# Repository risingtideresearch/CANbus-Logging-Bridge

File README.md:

# CANbus-Logging-Bridge
Platform for collecting, logging, interpreting, and relaying CAN messages on multiple busses

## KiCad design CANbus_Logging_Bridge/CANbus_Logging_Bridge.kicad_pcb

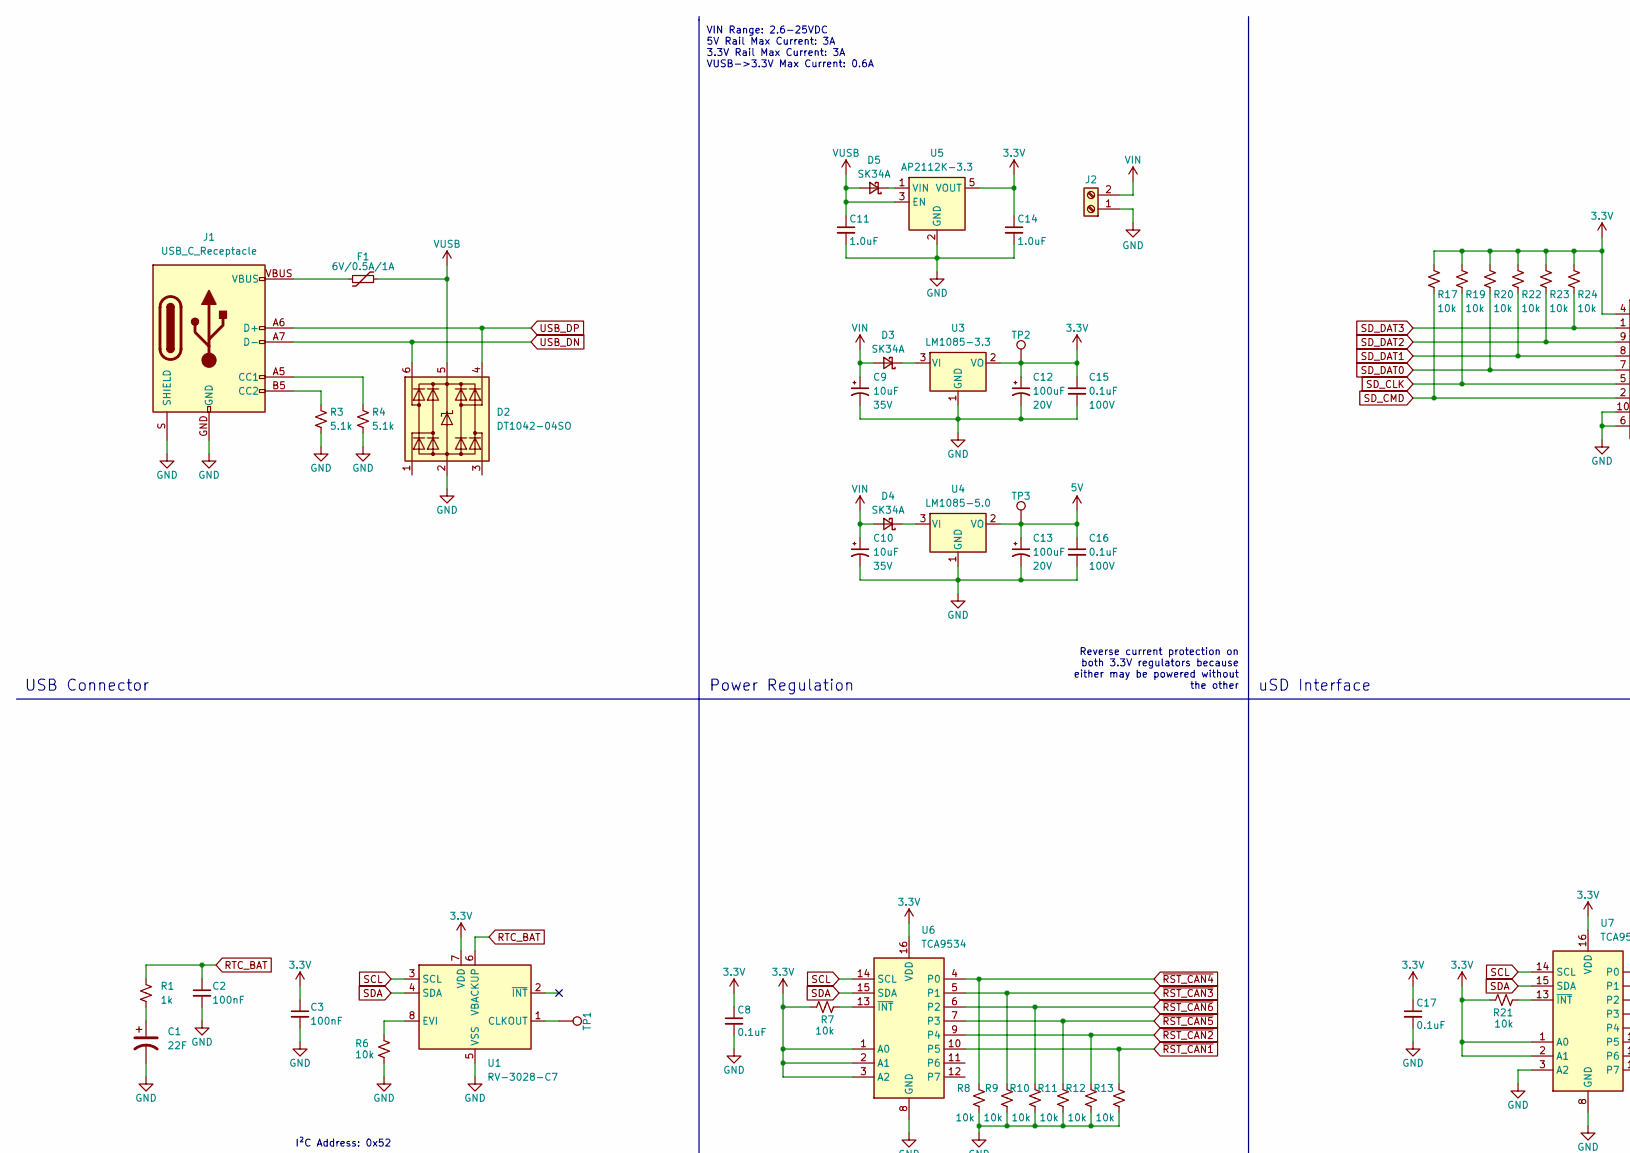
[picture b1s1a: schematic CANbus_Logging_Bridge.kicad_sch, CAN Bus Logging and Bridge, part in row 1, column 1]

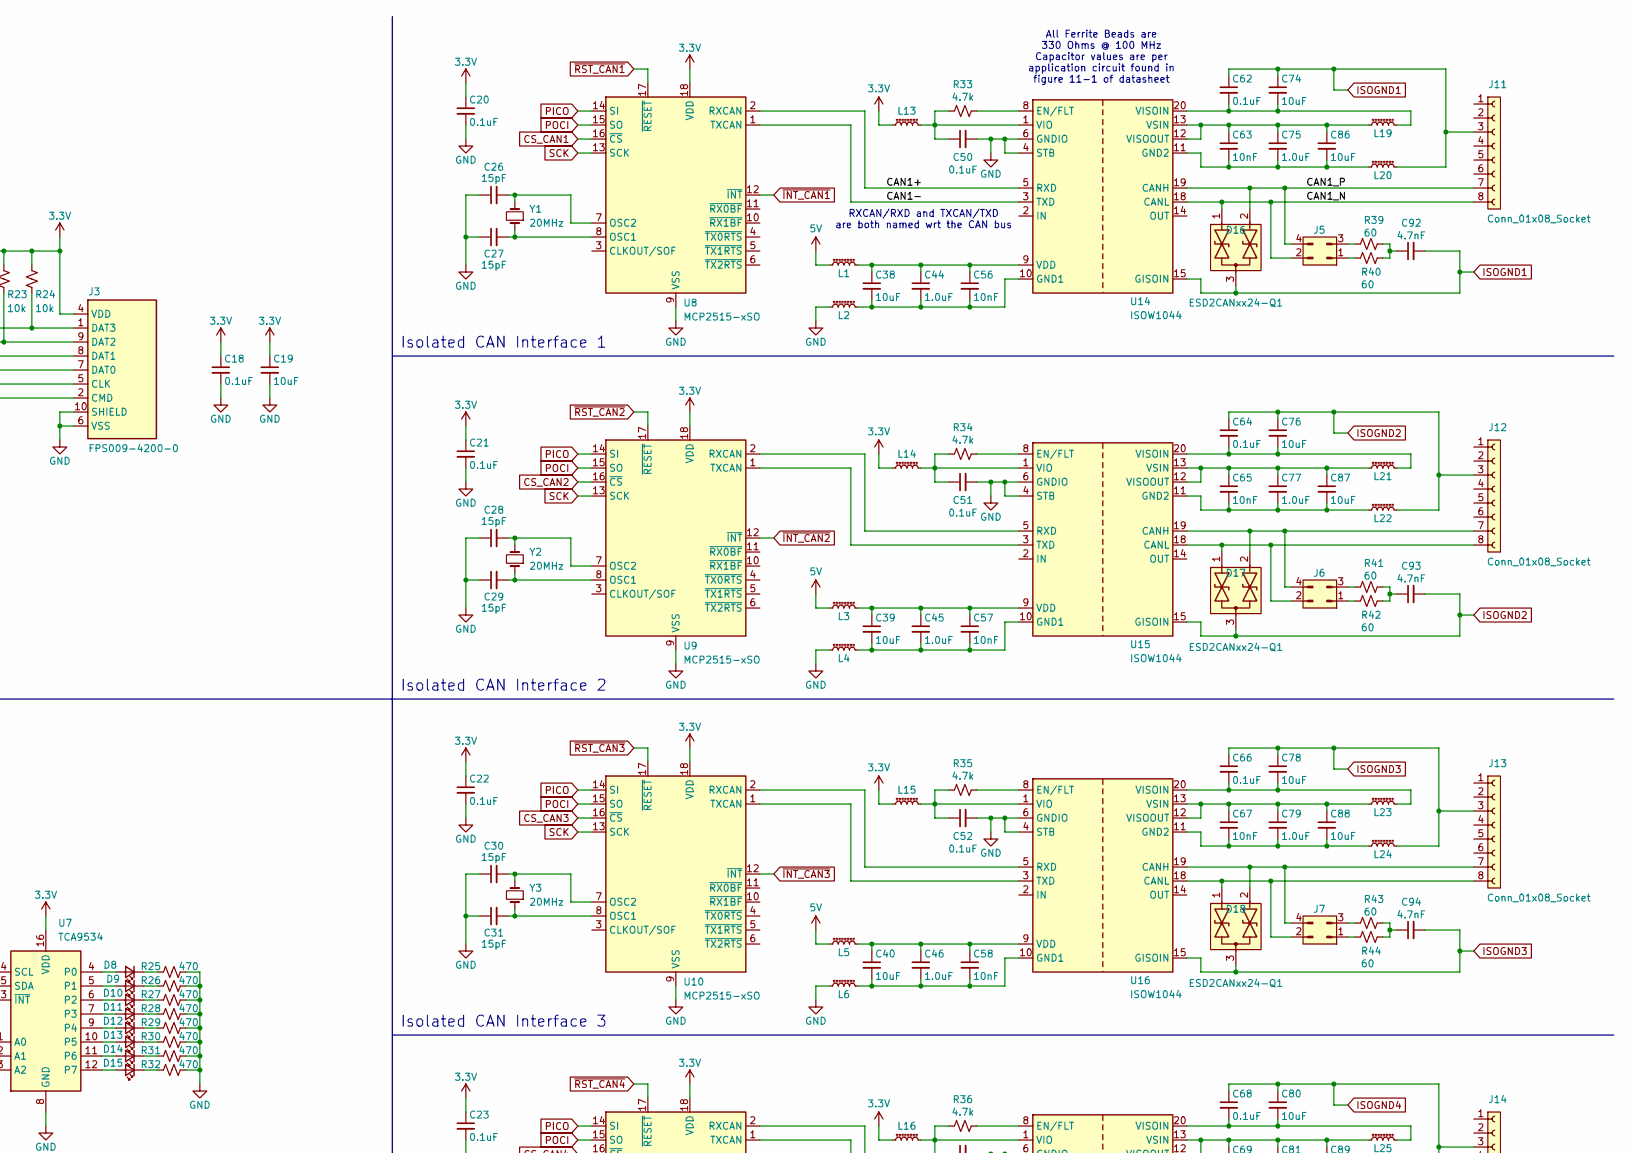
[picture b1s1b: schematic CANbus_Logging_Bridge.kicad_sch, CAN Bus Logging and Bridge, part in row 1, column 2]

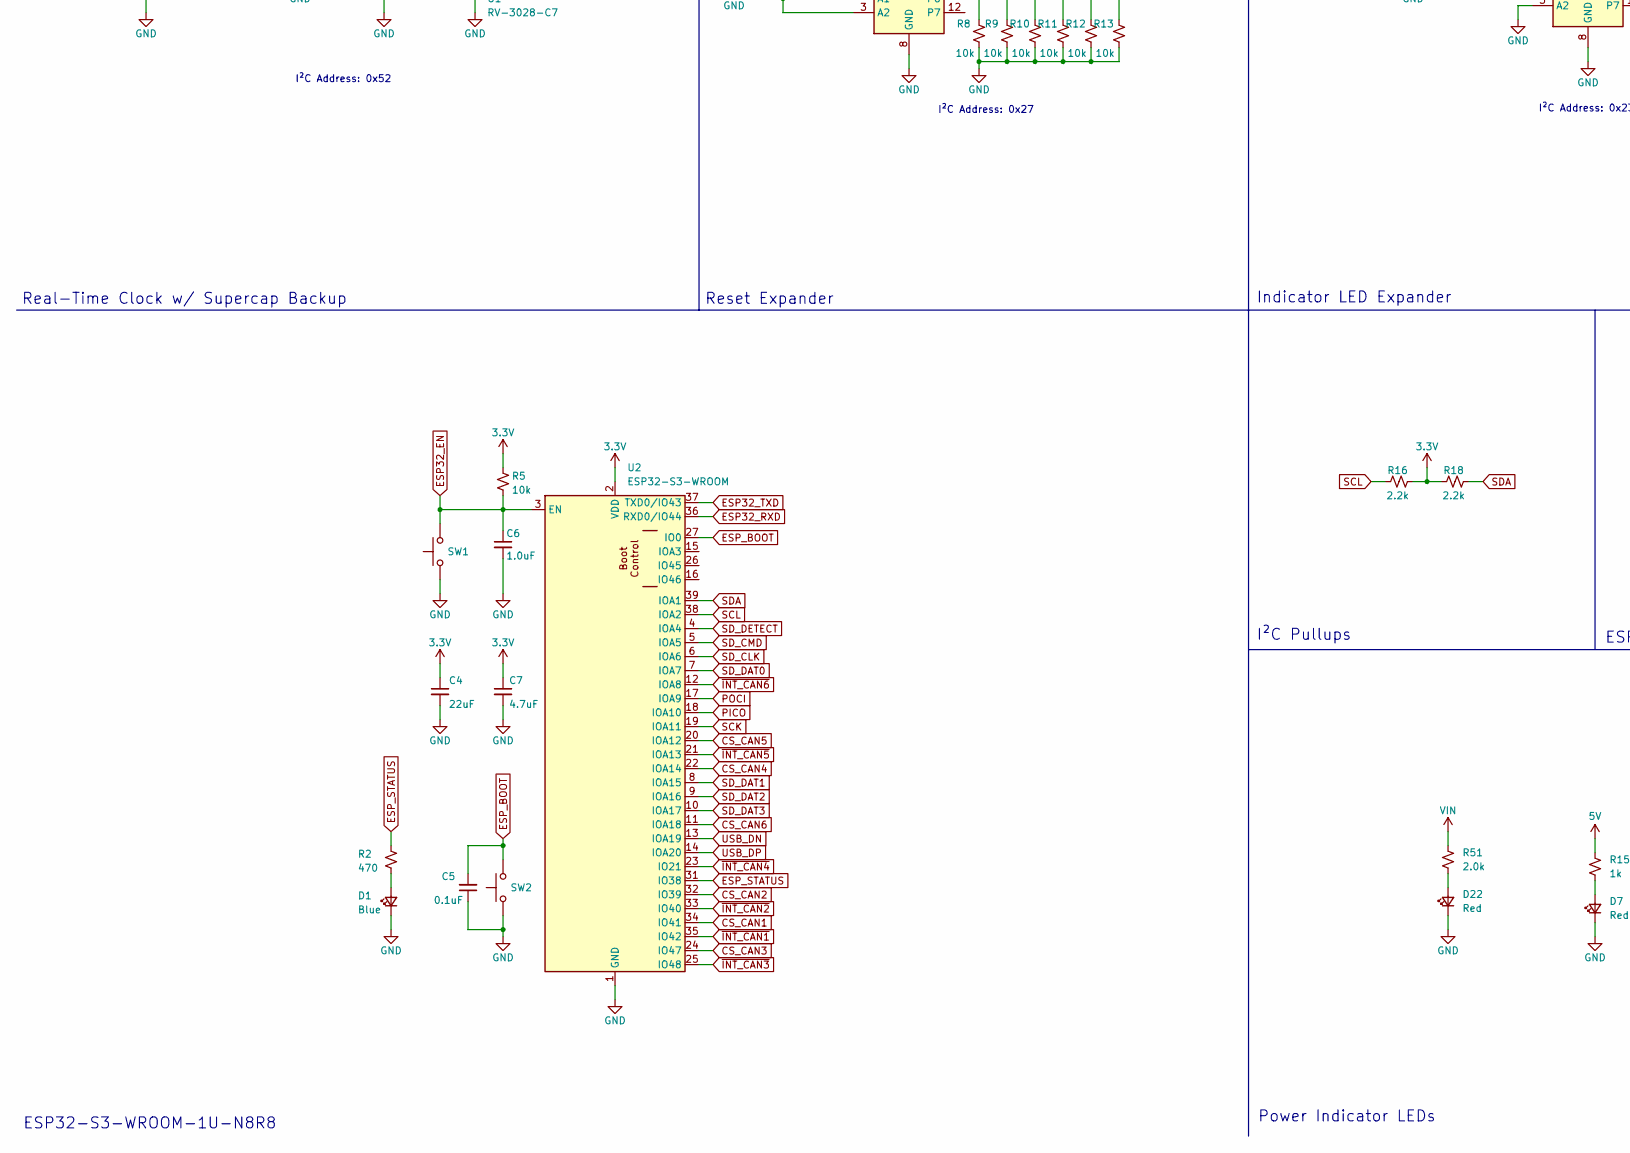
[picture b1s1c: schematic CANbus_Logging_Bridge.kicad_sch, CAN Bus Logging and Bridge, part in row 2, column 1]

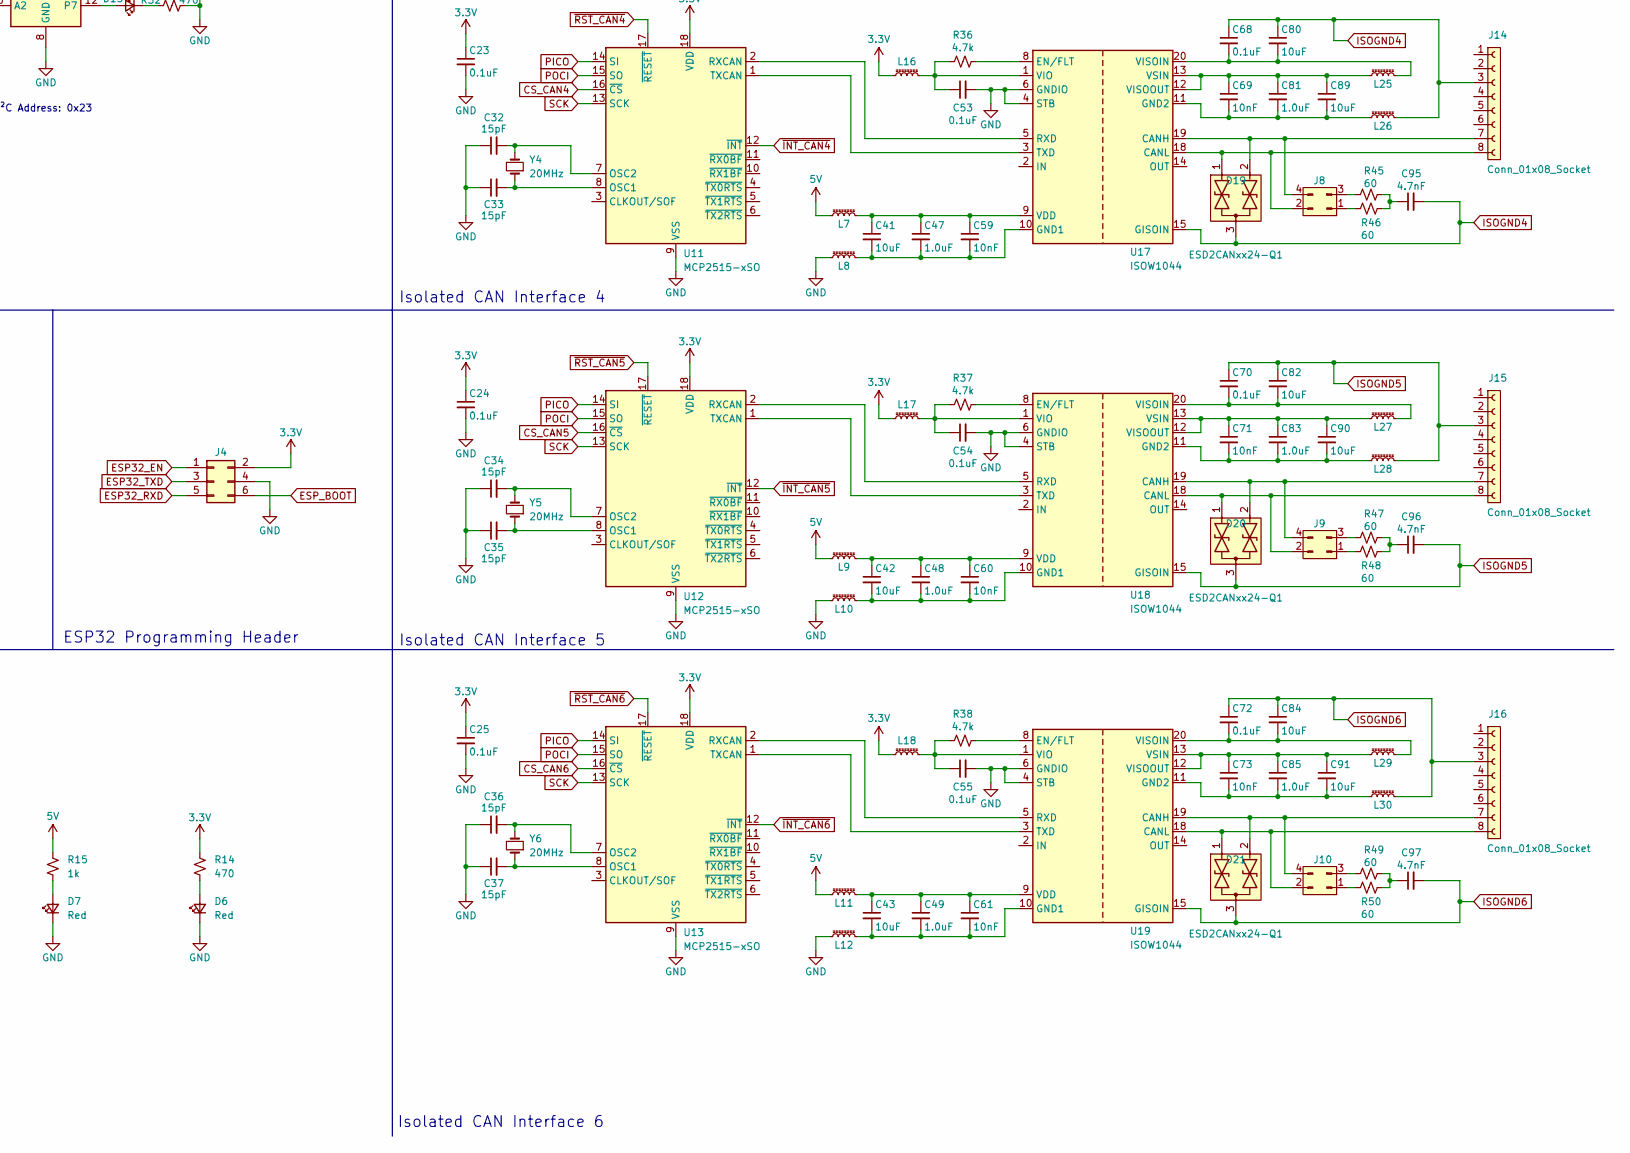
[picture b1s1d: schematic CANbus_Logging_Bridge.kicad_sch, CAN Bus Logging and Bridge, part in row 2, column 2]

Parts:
C1: 22F; 4.8_CoinCell_Dynacap
C2, C3: 100nF; C_0402_1005Metric; Voltage 25V; Tolerance 10%
C4: 22uF; C_0402_1005Metric; Voltage 6.3V; Tolerance 20%
C5, C8, C17, C18, C20, C21, C22, C23, C24, C25, C50, C51, C52, C53, C54, C55, C62, C64, C66, C68, C70, C72: 0.1uF; C_0402_1005Metric; Voltage 16V; Tolerance 10%
C6, C11, C14, C44, C45, C46, C47, C48, C49, C75, C77, C79, C81, C83, C85: 1.0uF; C_0402_1005Metric; Voltage 16V; Tolerance 10%
C7: 4.7uF; C_0402_1005Metric; Voltage 6.3V; Tolerance 20%
C9, C10: 10uF; CP_EIA-7343-30_AVX-N; Voltage 35V; Tolerance 20%
C12, C13: 100uF; CP_EIA-7343-30_AVX-N; Voltage 20V; Tolerance 10%
C15, C16: 0.1uF; C_0603_1608Metric; Voltage 100V; Tolerance 10%
C19, C38, C39, C40, C41, C42, C43, C74, C76, C78, C80, C82, C84, C86, C87, C88, C89, C90, C91: 10uF; C_0402_1005Metric; Voltage 6.3V; Tolerance 20%
C26, C27, C28, C29, C30, C31, C32, C33, C34, C35, C36, C37: 15pF; C_0402_1005Metric; Voltage 50V; Tolerance 5%
C56, C57, C58, C59, C60, C61, C63, C65, C67, C69, C71, C73: 10nF; C_0402_1005Metric; Voltage 25V; Tolerance 10%
C92, C93, C94, C95, C96, C97: 4.7nF; C_0402_1005Metric
D1, D8, D9, D10, D11, D12, D13, D14, D15: Blue; LED_0603_1608Metric
D2: DT1042-04SO; SOT23-6
D3, D4, D5: SK34A; SMA
D6, D7, D22: Red; LED_0603_1608Metric
D16, D17, D18, D19, D20, D21: ESD2CANxx24-Q1; SOT-323_SC-70
F1: 6V/0.5A/1A; 0805
J1: USB_C_Receptacle; USB-C_16
J2: Screw_Terminal_01x02; TerminalBlock_DoraboDBT10_8.5mm
J3: FPS009-4200-0; FPS00942000; Mouser Part Number 945-FPS009-4200-0
J4: Conn_02x03_Odd_Even; PinHeader_2x03_P2.54mm_Vertical
J5, J6, J7, J8, J9, J10: Conn_02x02_Pin; PinHeader_2x02_P2.54mm_Vertical_SMD
J11, J12, J13, J14, J15, J16: Conn_01x08_Socket; 1x08
L1, L2, L3, L4, L5, L6, L7, L8, L9, L10, L11, L12, L13, L14, L15, L16, L17, L18, L19, L20, L21, L22, L23, L24, L25, L26, L27, L28, L29, L30: 330 OHM; C_0402_1005Metric
R1, R15: 1k; R_0402_1005Metric
R2, R14, R25, R26, R27, R28, R29, R30, R31, R32: 470; R_0402_1005Metric
R3, R4: 5.1k; R_0402_1005Metric
R5, R6, R7, R8, R9, R10, R11, R12, R13, R17, R19, R20, R21, R22, R23, R24: 10k; R_0402_1005Metric
R16, R18: 2.2k; R_0402_1005Metric
R33, R34, R35, R36, R37, R38: 4.7k; R_0402_1005Metric
R39, R40, R41, R42, R43, R44, R45, R46, R47, R48, R49, R50: 60; R_0402_1005Metric
R51: 2.0k; R_1206_3216Metric
SW1, SW2: SMD_5.2x5.2mm_h1.9mm; Push_SMD_5.2x5.2mm_h1.9mm
TP1, TP2, TP3: 1.0mm; TestPoint-1.0mm
U1: RV-3028-C7; MicroCrystal_C7_SON-8_1.5x3.2mm_P0.9mm
U2: ESP32-S3-WROOM; ESP32-S3-WROOM-1U
U3: LM1085-3.3; TO-263-3_TabPin2
U4: LM1085-5.0; TO-263-3_TabPin2
U5: AP2112K-3.3; SOT23-5
U6, U7: TCA9534; SOIC-16W_7.5x10.3mm_P1.27mm
U8, U9, U10, U11, U12, U13: MCP2515-xSO; SOIC-18W_7.5x11.6mm_P1.27mm
U14, U15, U16, U17, U18, U19: ISOW1044; SOIC-20W_7.5x12.8mm_P1.27mm
Y1, Y2, Y3, Y4, Y5, Y6: 20MHz; Crystal_SMD_2.0x1.6mm

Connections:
3.3V: C3.1, C4.1, C7.1, C8.1, C12.1, C14.1, C15.1, C17.1, C18.1, C19.1, C20.1, C21.1, C22.1, C23.1, C24.1, C25.1, J3.4 (VDD), J4.2, L13.1, L14.1, L15.1, L16.1, L17.1, L18.1, R5.2, R7.1, R14.2, R16.1, R17.2, R18.2, R19.2, R20.2, R21.1, R22.2, R23.2, R24.2, TP2.1, U1.7 (VDD), U2.2 (VDD), U3.2 (VO), U5.5 (VOUT), U6.1 (A0), U6.2 (A1), U6.3 (A2), U6.16 (VDD), U7.1 (A0), U7.2 (A1), U7.16 (VDD), U8.18 (VDD), U9.18 (VDD), U10.18 (VDD), U11.18 (VDD), U12.18 (VDD), U13.18 (VDD)
5V: C13.1, C16.1, L1.1, L3.1, L5.1, L7.1, L9.1, L11.1, R15.2, TP3.1, U4.2 (VO)
/CAN1+: U8.2 (RXCAN), U14.5 (RXD)
/CAN1-: U8.1 (TXCAN), U14.3 (TXD)
/CAN1_N: D16.1 (A1), J5.2, J11.8, U14.18 (CANL)
/CAN1_P: D16.2 (A2), J5.4, J11.7, U14.19 (CANH)
CS_CAN1: U2.34 (IO41), U8.16 (~CS)
CS_CAN2: U2.32 (IO39), U9.16 (~CS)
CS_CAN3: U2.24 (IO47), U10.16 (~CS)
CS_CAN4: U2.22 (IOA14), U11.16 (~CS)
CS_CAN5: U2.20 (IOA12), U12.16 (~CS)
CS_CAN6: U2.11 (IOA18), U13.16 (~CS)
ESP32_EN: C6.1, J4.1, R5.1, SW1.2, U2.3 (EN)
ESP32_RXD: J4.5, U2.36 (RXD0/IO44)
ESP32_TXD: J4.3, U2.37 (TXD0/IO43)
ESP_BOOT: C5.2, J4.6, SW2.2, U2.27 (IO0)
ESP_STATUS: R2.2, U2.31 (IO38)
GND: C1.-, C2.2, C3.2, C4.2, C5.1, C6.2, C7.2, C8.2, C9.2, C10.2, C11.2, C12.2, C13.2, C14.2, C15.2, C16.2, C17.2, C18.2, C19.2, C20.2, C21.2, C22.2, C23.2, C24.2, C25.2, C26.1, C27.1, C28.1, C29.1, C30.1, C31.1, C32.1, C33.1, C34.1, C35.1, C36.1, C37.1, C50.2, C51.2, C52.2, C53.2, C54.2, C55.2, D1.1 (K), D2.2 (GND), D6.1 (K), D7.1 (K), D22.1 (K), J1.GND, J1.S (SHIELD), J2.1, J3.3 (VSS), J3.6 (VSS), J3.10 (SHIELD), J3.11 (SHIELD), J3.12 (SHIELD), J3.13 (SHIELD), J4.4, L2.1, L4.1, L6.1, L8.1, L10.1, L12.1, R3.1, R4.1, R6.1, R8.2, R9.2, R10.2, R11.2, R12.2, R13.2, R25.1, R26.1, R27.1, R28.1, R29.1, R30.1, R31.1, R32.1, SW1.1, SW2.1, U1.5 (VSS), U2.1 (GND), U2.40 (GND), U2.41.1 (GND), U2.41.2 (GND), U2.41.3 (GND), U2.41.4 (GND), U2.41.5 (GND), U2.41.6 (GND), U2.41.7 (GND), U2.41.8 (GND), U2.41.9 (GND), U3.1 (GND), U4.1 (GND), U5.2 (GND), U6.8 (GND), U7.3 (A2), U7.8 (GND), U8.9 (VSS), U9.9 (VSS), U10.9 (VSS), U11.9 (VSS), U12.9 (VSS), U13.9 (VSS), U14.4 (STB), U14.6 (GNDIO), U15.4 (STB), U15.6 (GNDIO), U16.4 (STB), U16.6 (GNDIO), U17.4 (STB), U17.6 (GNDIO), U18.4 (STB), U18.6 (GNDIO), U19.4 (STB), U19.6 (GNDIO)
unnamed: C1.+, R1.1
unnamed: C92.1, R39.1, R40.1
unnamed: C93.1, R41.1, R42.1
unnamed: C94.1, R43.1, R44.1
unnamed: C95.1, R45.1, R46.1
unnamed: C96.1, R47.1, R48.1
unnamed: C97.1, R49.1, R50.1
unnamed: D1.2 (A), R2.1
unnamed: D3.C (K), U3.3 (VI)
unnamed: D4.C (K), U4.3 (VI)
unnamed: D5.C (K), U5.1 (VIN)
unnamed: D6.2 (A), R14.1
unnamed: D7.2 (A), R15.1
unnamed: D8.2 (A), U7.4 (P0)
unnamed: D8.1 (K), R25.2
unnamed: D9.2 (A), U7.5 (P1)
unnamed: D9.1 (K), R26.2
unnamed: D10.2 (A), U7.6 (P2)
unnamed: D10.1 (K), R27.2
unnamed: D11.2 (A), U7.7 (P3)
unnamed: D11.1 (K), R28.2
unnamed: D12.2 (A), U7.9 (P4)
unnamed: D12.1 (K), R29.2
unnamed: D13.2 (A), U7.10 (P5)
unnamed: D13.1 (K), R30.2
unnamed: D14.2 (A), U7.11 (P6)
unnamed: D14.1 (K), R31.2
unnamed: D15.2 (A), U7.12 (P7)
unnamed: D15.1 (K), R32.2
unnamed: D17.1 (A1), J6.2, J12.8, U15.18 (CANL)
unnamed: D17.2 (A2), J6.4, J12.7, U15.19 (CANH)
unnamed: D18.1 (A1), J7.2, J13.8, U16.18 (CANL)
unnamed: D18.2 (A2), J7.4, J13.7, U16.19 (CANH)
unnamed: D19.1 (A1), J8.2, J14.8, U17.18 (CANL)
unnamed: D19.2 (A2), J8.4, J14.7, U17.19 (CANH)
unnamed: D20.1 (A1), J9.2, J15.8, U18.18 (CANL)
unnamed: D20.2 (A2), J9.4, J15.7, U18.19 (CANH)
unnamed: D21.1 (A1), J10.2, J16.8, U19.18 (CANL)
unnamed: D21.2 (A2), J10.4, J16.7, U19.19 (CANH)
unnamed: D22.2 (A), R51.1
unnamed: F1.1, J1.VBUS
unnamed: J1.A5 (CC1), R4.2
unnamed: J1.B5 (CC2), R3.2
unnamed: J5.1, R40.2
unnamed: J5.3, R39.2
unnamed: J6.1, R42.2
unnamed: J6.3, R41.2
unnamed: J7.1, R44.2
unnamed: J7.3, R43.2
unnamed: J8.1, R46.2
unnamed: J8.3, R45.2
unnamed: J9.1, R48.2
unnamed: J9.3, R47.2
unnamed: J10.1, R50.2
unnamed: J10.3, R49.2
unnamed: TP1.1, U1.1 (CLKOUT)
unnamed: R6.2, U1.8 (EVI)
unnamed: R7.2, U6.13 (~INT)
unnamed: R21.2, U7.13 (~INT)
unnamed: C27.2, U8.8 (OSC1), Y1.1
unnamed: C26.2, U8.7 (OSC2), Y1.2
unnamed: C29.2, U9.8 (OSC1), Y2.1
unnamed: C28.2, U9.7 (OSC2), Y2.2
unnamed: C31.2, U10.8 (OSC1), Y3.1
unnamed: C30.2, U10.7 (OSC2), Y3.2
unnamed: U10.2 (RXCAN), U16.5 (RXD)
unnamed: U10.1 (TXCAN), U16.3 (TXD)
unnamed: C33.2, U11.8 (OSC1), Y4.1
unnamed: C32.2, U11.7 (OSC2), Y4.2
unnamed: U11.2 (RXCAN), U17.5 (RXD)
unnamed: U11.1 (TXCAN), U17.3 (TXD)
unnamed: C35.2, U12.8 (OSC1), Y5.1
unnamed: C34.2, U12.7 (OSC2), Y5.2
unnamed: U12.2 (RXCAN), U18.5 (RXD)
unnamed: U12.1 (TXCAN), U18.3 (TXD)
unnamed: C37.2, U13.8 (OSC1), Y6.1
unnamed: C36.2, U13.7 (OSC2), Y6.2
unnamed: U13.2 (RXCAN), U19.5 (RXD)
unnamed: U13.1 (TXCAN), U19.3 (TXD)
unnamed: R33.2, U14.8 (EN/FLT)
unnamed: C38.2, C44.2, C56.2, L2.2, U14.10 (GND1)
unnamed: C63.2, C75.2, C86.2, L20.1, U14.11 (GND2)
unnamed: C38.1, C44.1, C56.1, L1.2, U14.9 (VDD)
unnamed: C50.1, L13.2, R33.1, U14.1 (VIO)
unnamed: C62.2, C74.2, L19.2, U14.20 (VISOIN)
unnamed: C63.1, C75.1, C86.1, L19.1, U14.12 (VISOOUT), U14.13 (VSIN)
unnamed: R34.2, U15.8 (EN/FLT)
unnamed: C39.2, C45.2, C57.2, L4.2, U15.10 (GND1)
unnamed: C65.2, C77.2, C87.2, L22.1, U15.11 (GND2)
unnamed: U9.2 (RXCAN), U15.5 (RXD)
unnamed: U9.1 (TXCAN), U15.3 (TXD)
unnamed: C39.1, C45.1, C57.1, L3.2, U15.9 (VDD)
unnamed: C51.1, L14.2, R34.1, U15.1 (VIO)
unnamed: C64.2, C76.2, L21.2, U15.20 (VISOIN)
unnamed: C65.1, C77.1, C87.1, L21.1, U15.12 (VISOOUT), U15.13 (VSIN)
unnamed: R35.2, U16.8 (EN/FLT)
unnamed: C40.2, C46.2, C58.2, L6.2, U16.10 (GND1)
unnamed: C67.2, C79.2, C88.2, L24.1, U16.11 (GND2)
unnamed: C40.1, C46.1, C58.1, L5.2, U16.9 (VDD)
unnamed: C52.1, L15.2, R35.1, U16.1 (VIO)
unnamed: C66.2, C78.2, L23.2, U16.20 (VISOIN)
unnamed: C67.1, C79.1, C88.1, L23.1, U16.12 (VISOOUT), U16.13 (VSIN)
unnamed: R36.2, U17.8 (EN/FLT)
unnamed: C41.2, C47.2, C59.2, L8.2, U17.10 (GND1)
unnamed: C69.2, C81.2, C89.2, L26.1, U17.11 (GND2)
unnamed: C41.1, C47.1, C59.1, L7.2, U17.9 (VDD)
unnamed: C53.1, L16.2, R36.1, U17.1 (VIO)
unnamed: C68.2, C80.2, L25.2, U17.20 (VISOIN)
unnamed: C69.1, C81.1, C89.1, L25.1, U17.12 (VISOOUT), U17.13 (VSIN)
unnamed: R37.2, U18.8 (EN/FLT)
unnamed: C42.2, C48.2, C60.2, L10.2, U18.10 (GND1)
unnamed: C71.2, C83.2, C90.2, L28.1, U18.11 (GND2)
unnamed: C42.1, C48.1, C60.1, L9.2, U18.9 (VDD)
unnamed: C54.1, L17.2, R37.1, U18.1 (VIO)
unnamed: C70.2, C82.2, L27.2, U18.20 (VISOIN)
unnamed: C71.1, C83.1, C90.1, L27.1, U18.12 (VISOOUT), U18.13 (VSIN)
unnamed: R38.2, U19.8 (EN/FLT)
unnamed: C43.2, C49.2, C61.2, L12.2, U19.10 (GND1)
unnamed: C73.2, C85.2, C91.2, L30.1, U19.11 (GND2)
unnamed: C43.1, C49.1, C61.1, L11.2, U19.9 (VDD)
unnamed: C55.1, L18.2, R38.1, U19.1 (VIO)
unnamed: C72.2, C84.2, L29.2, U19.20 (VISOIN)
unnamed: C73.1, C85.1, C91.1, L29.1, U19.12 (VISOOUT), U19.13 (VSIN)
PICO: U2.18 (IOA10), U8.14 (SI), U9.14 (SI), U10.14 (SI), U11.14 (SI), U12.14 (SI), U13.14 (SI)
POCI: U2.17 (IOA9), U8.15 (SO), U9.15 (SO), U10.15 (SO), U11.15 (SO), U12.15 (SO), U13.15 (SO)
RTC_BAT: C2.1, R1.2, U1.6 (VBACKUP)
SCK: U2.19 (IOA11), U8.13 (SCK), U9.13 (SCK), U10.13 (SCK), U11.13 (SCK), U12.13 (SCK), U13.13 (SCK)
SCL: R16.2, U1.3 (SCL), U2.38 (IOA2), U6.14 (SCL), U7.14 (SCL)
SDA: R18.1, U1.4 (SDA), U2.39 (IOA1), U6.15 (SDA), U7.15 (SDA)
SD_CLK: J3.5 (CLK), R19.1, U2.6 (IOA6)
SD_CMD: J3.2 (CMD), R17.1, U2.5 (IOA5)
SD_DAT0: J3.7 (DAT0), R20.1, U2.7 (IOA7)
SD_DAT1: J3.8 (DAT1), R22.1, U2.8 (IOA15)
SD_DAT2: J3.9 (DAT2), R23.1, U2.9 (IOA16)
SD_DAT3: J3.1 (DAT3), R24.1, U2.10 (IOA17)
SD_DETECT: U2.4 (IOA4)
USB_DN: D2.6 (I/O4), J1.A7 (D-), J1.B7 (D-), U2.13 (IOA19)
USB_DP: D2.4 (I/O3), J1.A6 (D+), J1.B6 (D+), U2.14 (IOA20)
VIN: C9.1, C10.1, D3.A, D4.A, J2.2, R51.2
VUSB: C11.1, D2.5 (VCC), D5.A, F1.2, U5.3 (EN)
~INT_CAN1: U2.35 (IO42), U8.12 (~INT)
~INT_CAN2: U2.33 (IO40), U9.12 (~INT)
~INT_CAN3: U2.25 (IO48), U10.12 (~INT)
~INT_CAN4: U2.23 (IO21), U11.12 (~INT)
~INT_CAN5: U2.21 (IOA13), U12.12 (~INT)
~INT_CAN6: U2.12 (IOA8), U13.12 (~INT)
~RST_CAN1: R13.1, U6.10 (P5), U8.17 (~RESET)
~RST_CAN2: R12.1, U6.9 (P4), U9.17 (~RESET)
~RST_CAN3: R9.1, U6.5 (P1), U10.17 (~RESET)
~RST_CAN4: R8.1, U6.4 (P0), U11.17 (~RESET)
~RST_CAN5: R11.1, U6.7 (P3), U12.17 (~RESET)
~RST_CAN6: R10.1, U6.6 (P2), U13.17 (~RESET)

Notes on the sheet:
Indicator LED Expander
Reverse current protection on both 3.3V regulators because either may be powered without the other
Power Regulation
Isolated CAN Interface 4
I²C Address: 0x27
VIN Range: 2.6-25VDC 5V Rail Max Current: 3A 3.3V Rail Max Current: 3A VUSB->3.3V Max Current: 0.6A
ESP32-S3-WROOM-1U-N8R8
I²C Address: 0x52
RXCAN/RXD and TXCAN/TXD are both named wrt the CAN bus
I²C Pullups
Isolated CAN Interface 5
Isolated CAN Interface 3
Reset Expander
USB Connector
Isolated CAN Interface 6
ESP32 Programming Header
Real-Time Clock w/ Supercap Backup
Isolated CAN Interface 1
I²C Address: 0x23
uSD Interface
Isolated CAN Interface 2
Power Indicator LEDs
All Ferrite Beads are 330 Ohms @ 100 MHz Capacitor values are per application circuit found in figure 11-1 of datasheet

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
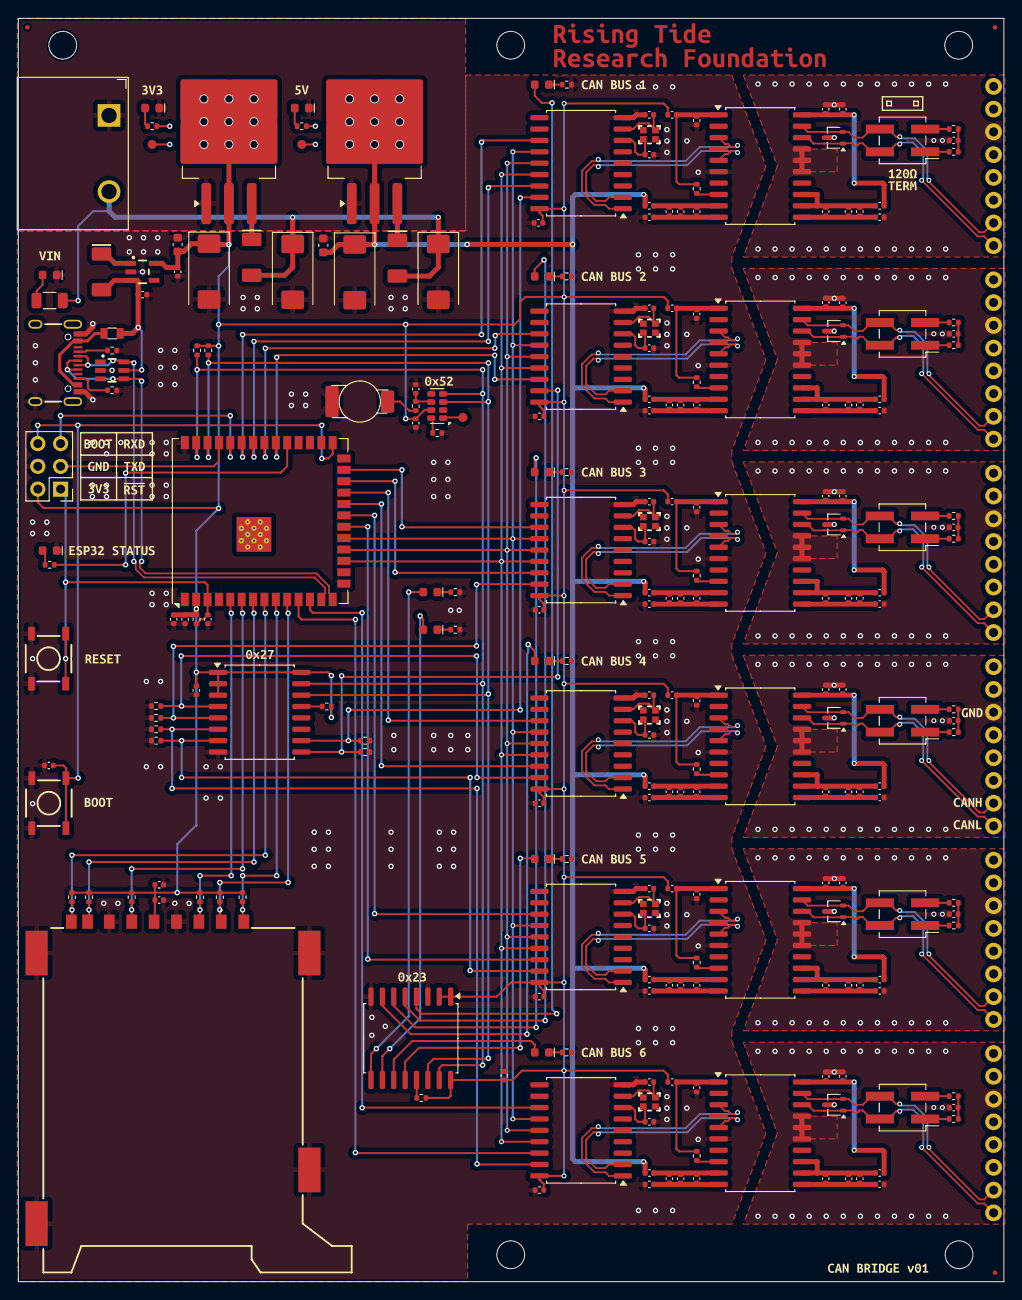
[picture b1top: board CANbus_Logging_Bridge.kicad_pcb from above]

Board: 4 copper layers, 110.0 x 141.0 mm, 278 parts (1 on the bottom side), 175 nets.

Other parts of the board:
Ref**: Fiducial_0.5mm_Mask1mm
Ref**#2, Ref**#3: Fiducial_0.5mm_Mask1mm
kibuzzard-683381FB: G***; kibuzzard-683381FB
kibuzzard-683384E4: G***; kibuzzard-683384E4
kibuzzard-683384F2: G***; kibuzzard-683384F2
kibuzzard-683385A1: G***; kibuzzard-683385A1
kibuzzard-683385A6: G***; kibuzzard-683385A6
kibuzzard-683390BD: G***; kibuzzard-683390BD
kibuzzard-683390C2: G***; kibuzzard-683390C2
kibuzzard-683390DA: G***; kibuzzard-683390DA
kibuzzard-683390E1: G***; kibuzzard-683390E1
kibuzzard-683390E7: G***; kibuzzard-683390E7
kibuzzard-683393CD: G***; kibuzzard-683393CD
kibuzzard-6833820A: G***; kibuzzard-6833820A
kibuzzard-6833851A: G***; kibuzzard-6833851A
kibuzzard-6833856B: G***; kibuzzard-6833856B
kibuzzard-6833858D: G***; kibuzzard-6833858D
kibuzzard-6833859C: G***; kibuzzard-6833859C
kibuzzard-6833916E: G***; kibuzzard-6833916E
kibuzzard-6833918D: G***; kibuzzard-6833918D
kibuzzard-6833959C: G***; kibuzzard-6833959C
kibuzzard-68338202: G***; kibuzzard-68338202
kibuzzard-68338593: G***; kibuzzard-68338593
kibuzzard-68338682: G***; kibuzzard-68338682
kibuzzard-68339090: G***; kibuzzard-68339090
kibuzzard-68339145: G***; kibuzzard-68339145
kibuzzard-68339228: G***; kibuzzard-68339228
kibuzzard-68339419: G***; kibuzzard-68339419
kibuzzard-68339449: G***; kibuzzard-68339449
kibuzzard-68339454: G***; kibuzzard-68339454

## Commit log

2025-05-06 Initial Commit
    Initial circuit design
    No changes made since 5/5 meeting
    Pushing for review
2025-05-25 v01 layout pre-silk
    Project:
    -Add datasheets
    SCH:
    -Add termination resistors/jumpers to CAN lines
    -Swap microSD socket to full SD socket
    -Change RJ45 pinout to VE.Can pinout
2025-05-25 Layout v01
    -Add Silk
    -Ground Stitching
2025-06-24 Migrate to RisingTideResearch-Libs
    - Change all component references to the new KiCad libraries
    - Remove datasheets directory as datasheets are now embedded
2025-07-24 Update all symbols and footprints from lib
    - Update symbols and footprints (lib updated with LCSC part numbers)
    - Replace 60R resistors with closest E96 value (60.4R)
2025-12-16 Upload prototype firmware in progress
    It doesn't compile at the moment, I was caught in the middle of some changes
2025-12-28 Update Gateway_Test_Integrated_multiwrite_lint.ino
    Doing too much in the ISR, committing for posterity.
    Menu is most pleasant to navigate in Realterm with Ansi display in NewLine mode (or equivalent terminal emulator)
2026-01-06 Update Gateway_Test_Integrated_multiwrite_lint.ino
    Firmware now logs all six channels at near saturation.
    - Create struct for CAN frames
    - Expand SD write buffer
    - Declare `volatile` for globals that are touched by ISR
    - Declare `const` for pin-assignment arrays
    - Add serial debug stuff to monitor ring buffers
2026-01-13 Update Gateway_Test_Integrated_multiwrite_lint.ino
    - Add struct members to CANFrame for frame metadata
    - Add expandFrame() to translate raw MCP register bytes to frame metadata
    - Fix log formatting
    - Add timestamps using POSIX style gettimeofday() calls
    - Move tasks and core assignments around in an attempt to solve assumed SPI driver (possibly GPIO matrix?) delays.
    - Change delays in main loops to non-blocking delays to ensure watchdogs get fed
2026-02-22 Layout and routing for v02
    - New 4-Layer layout
    - Swap out MCP2515 for MCP2518 (double the SPI bus speed + FIFO + Timestamping)
    - Split SPI bus (remove interrupt lines to make room, change to polling approach)
    - Swap Linear Regs out for Switching Regs
    - Add Test Points
    - Add LED indicators to TTL level RXCAN/TXCAN lines as activity indicators
2026-02-26 CAN Gateway V02 ready for review
    - Change Project Name
    - Add Silkscreen
    - Add Outline and Standoffs
    - Add GPIO Test Points
2026-03-02 Quick Fix to v02
    - Route CS traces for CAN (Thanks Jeff!)
    - Remove VUSB regulator. USB no longer powers device.
